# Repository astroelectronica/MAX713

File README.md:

# MAX713
NiCd/NiMH Battery Fast-Charge Controller

AE01012713

https://www.analog.com/en/products/max713.html

https://www.analog.com/en/resources/evaluation-hardware-and-software/evaluation-boards-kits/max713swevkit.html

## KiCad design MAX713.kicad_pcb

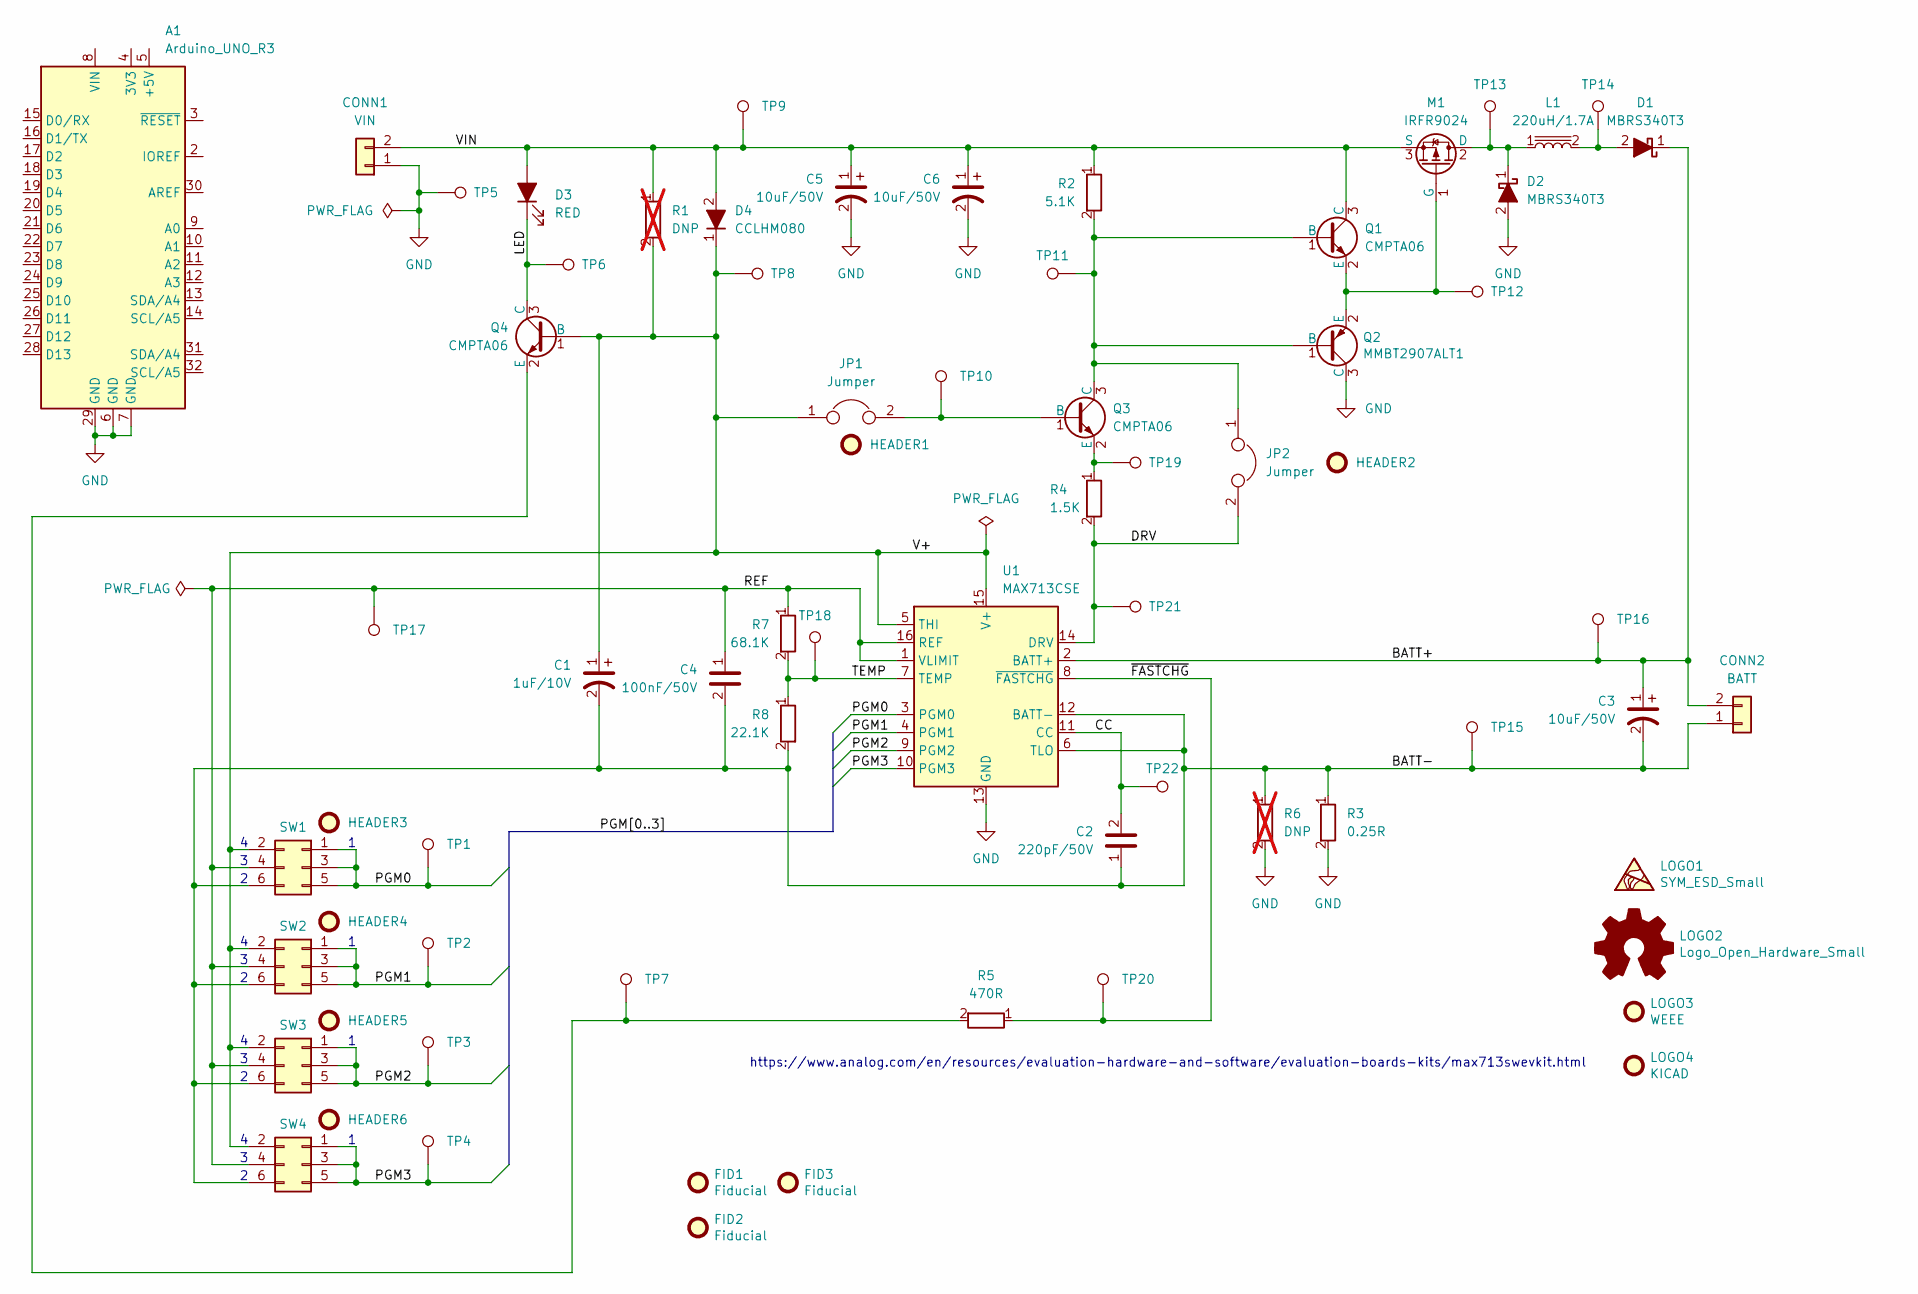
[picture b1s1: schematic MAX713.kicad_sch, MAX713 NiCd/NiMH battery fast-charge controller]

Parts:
A1: Arduino_UNO_R3; Arduino_UNO_R3_WithMountingHoles
C1: 1uF/10V; CP_EIA-3528-21_Kemet-B; MPN 595D105X9035A2T
C2: 220pF/50V; C_0805_2012Metric; MPN C0805C221J5GACTU
C3, C5, C6: 10uF/50V; CP_EIA-7260-38_AVX-R; MPN 595D106X0050R2T
C4: 100nF/50V; C_0805_2012Metric; MPN C0805C101J5GAC7800
CONN1: VIN; TerminalBlock_Phoenix_MKDS-1,5-2-5.08_1x02_P5.08mm_Horizont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; MPN 1985865
CONN2: BATT; TerminalBlock_Phoenix_MKDS-1,5-2-5.08_1x02_P5.08mm_Horizont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; MPN 1985865
D1, D2: MBRS340T3; D_SMC; MPN MBRS340T3G
D3: RED; LED_1206_3216Metric_ReverseMount_Hole1.8x2.4mm; MPN SML-211UTT86
D4: CCLHM080; D_MiniMELF; MPN CMJH080 TR PBFREE
FID1, FID2, FID3: Fiducial; Fiducial_1mm_Mask2mm
HEADER1, HEADER2, HEADER3, HEADER4, HEADER5, HEADER6: 929950-00; MPN 929950-00
JP1, JP2: Jumper; PinHeader_1x02_P2.54mm_Vertical; MPN 5-146281-2
L1: 220uH/1.7A; L_Bourns_SRR1210A; MPN SRR1210-221M
LOGO1: SYM_ESD_Small; ESD-Logo_6.6x6mm_SilkScreen
LOGO2: Logo_Open_Hardware_Small; OSHW-Logo_5.7x6mm_SilkScreen
LOGO3: WEEE; WEEE-Logo_4.2x6mm_SilkScreen
LOGO4: KICAD; KiCad-Logo2_5mm_SilkScreen
M1: IRFR9024; TO-252-2; MPN IRFR9024TRPBF
Q1, Q3, Q4: CMPTA06; SOT-23; MPN CMPTA06 TR PBFREE
Q2: MMBT2907ALT1; SOT-23; MPN MMBT2907ALT1G
R1, R6: DNP; R_Axial_DIN0922_L20.0mm_D9.0mm_P30.48mm_Horizontal; not fitted
R2: 5.1K; R_0805_2012Metric; MPN CRCW08055K10FKEA
R3: 0.25R; R_2512_6332Metric; MPN WSL2512R2500FEA
R4: 1.5K; R_0805_2012Metric; MPN CRCW08051K50FKEA
R5: 470R; R_0805_2012Metric; MPN CRCW0805470RFKEA
R7: 68.1K; R_0805_2012Metric; MPN CRCW080568K1FKEA
R8: 22.1K; R_0805_2012Metric; MPN CRCW080522K1FKEA
SW1: SW1; PinHeader_2x03_P2.54mm_Vertical; MPN 67996-206HLF
SW2: SW2; PinHeader_2x03_P2.54mm_Vertical; MPN 67996-206HLF
SW3: SW3; PinHeader_2x03_P2.54mm_Vertical; MPN 67996-206HLF
SW4: SW4; PinHeader_2x03_P2.54mm_Vertical; MPN 67996-206HLF
TP1, TP2, TP3, TP4, TP5, TP6, TP7, TP8, TP9, TP10, TP11, TP12, TP13, TP14, TP15, TP16, TP17, TP18, TP19, TP20, TP21, TP22: TestPoint; TestPoint_Pad_D1.5mm
U1: MAX713CSE; SOIC-16_3.9x9.9mm_P1.27mm; MPN MAX713CSE+

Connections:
/BATT+: C3.1, CONN2.2, D1.1 (K), TP16.1, U1.2 (BATT+)
/BATT-: C1.2, C2.1, C3.2, C4.2, CONN2.1, R3.1, R6.1, R8.2, SW1.6, SW2.6, SW3.6, SW4.6, TP15.1, U1.6 (TLO), U1.12 (BATT-)
/CC: C2.2, TP22.1, U1.11 (CC)
/DRV: JP2.2, R4.2, TP21.1, U1.14 (DRV)
/LED: D3.1 (K), Q4.3 (C), TP6.1
/PGM0: SW1.1, SW1.3, SW1.5, TP1.1, U1.3 (PGM0)
/PGM1: SW2.1, SW2.3, SW2.5, TP2.1, U1.4 (PGM1)
/PGM2: SW3.1, SW3.3, SW3.5, TP3.1, U1.9 (PGM2)
/PGM3: SW4.1, SW4.3, SW4.5, TP4.1, U1.10 (PGM3)
/REF: C4.1, R7.1, SW1.4, SW2.4, SW3.4, SW4.4, TP17.1, U1.1 (VLIMIT), U1.16 (REF)
/TEMP: R7.2, R8.1, TP18.1, U1.7 (TEMP)
/V+: C1.1, D4.1 (K), JP1.1, Q4.1 (B), R1.2, SW1.2, SW2.2, SW3.2, SW4.2, TP8.1, U1.5 (THI), U1.15 (V+)
/VIN: C5.1, C6.1, CONN1.2, D3.2 (A), D4.2 (A), M1.3 (S), Q1.3 (C), R1.1, R2.1, TP9.1
/~FASTCHG: R5.1, TP20.1, U1.8 (~FASTCHG)
GND: A1.6 (GND), A1.7 (GND), A1.29 (GND), C5.2, C6.2, CONN1.1, D2.2 (A), Q2.3 (C), R3.2, R6.2, TP5.1, U1.13 (GND)
unnamed: D1.2 (A), L1.2, TP14.1
unnamed: D2.1 (K), L1.1, M1.2 (D), TP13.1
unnamed: M1.1 (G), Q1.2 (E), Q2.2 (E), TP12.1
unnamed: JP2.1, Q1.1 (B), Q2.1 (B), Q3.3 (C), R2.2, TP11.1
unnamed: JP1.2, Q3.1 (B), TP10.1
unnamed: Q3.2 (E), R4.1, TP19.1
unnamed: Q4.2 (E), R5.2, TP7.1

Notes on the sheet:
https://www.analog.com/en/resources/evaluation-hardware-and-software/evaluation-boards-kits/max713swevkit.html

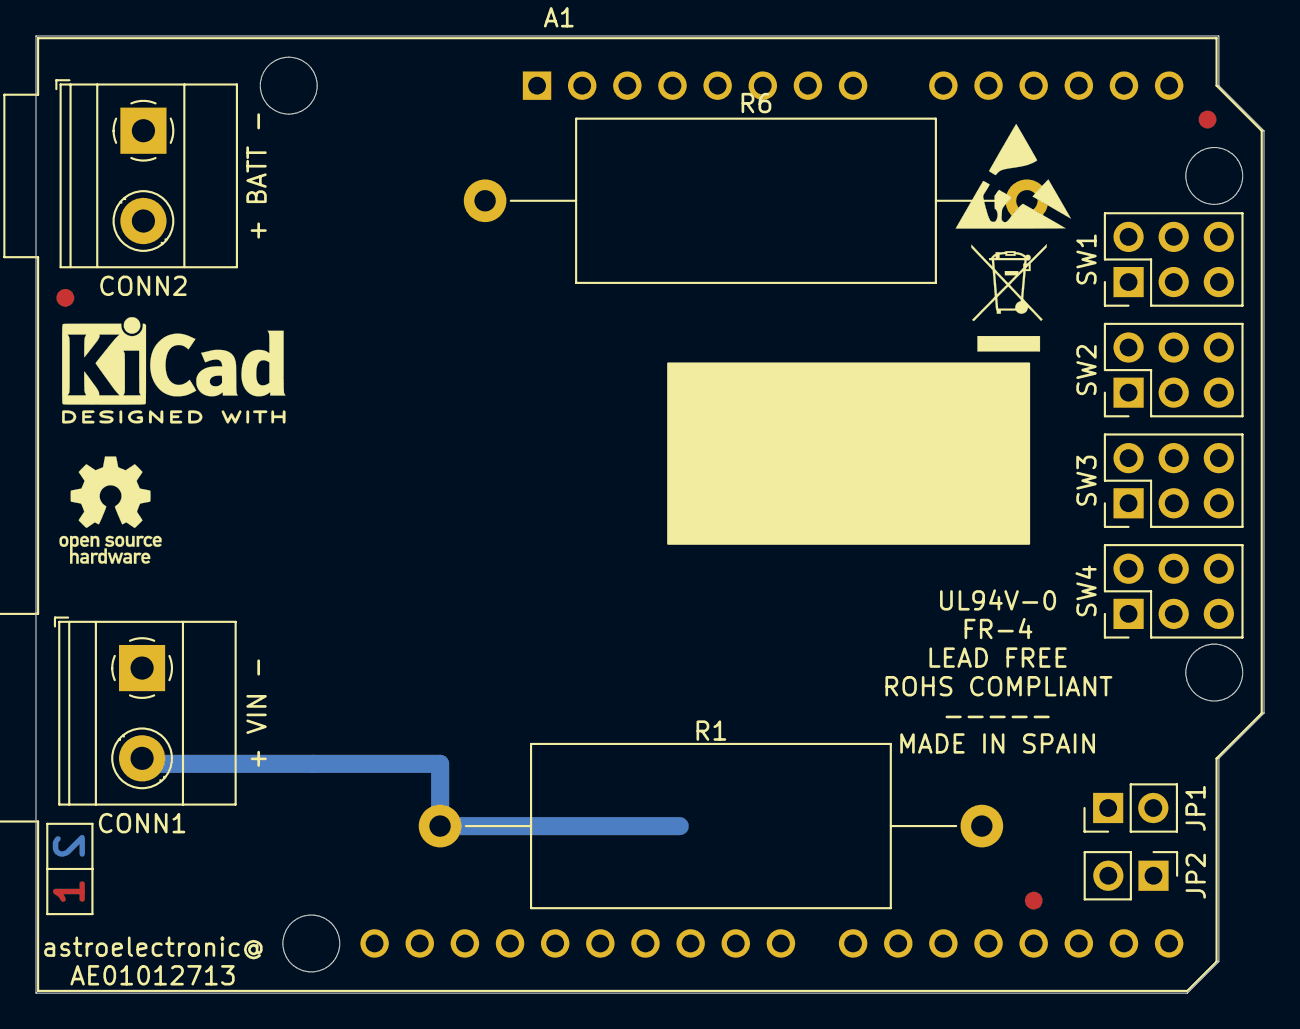
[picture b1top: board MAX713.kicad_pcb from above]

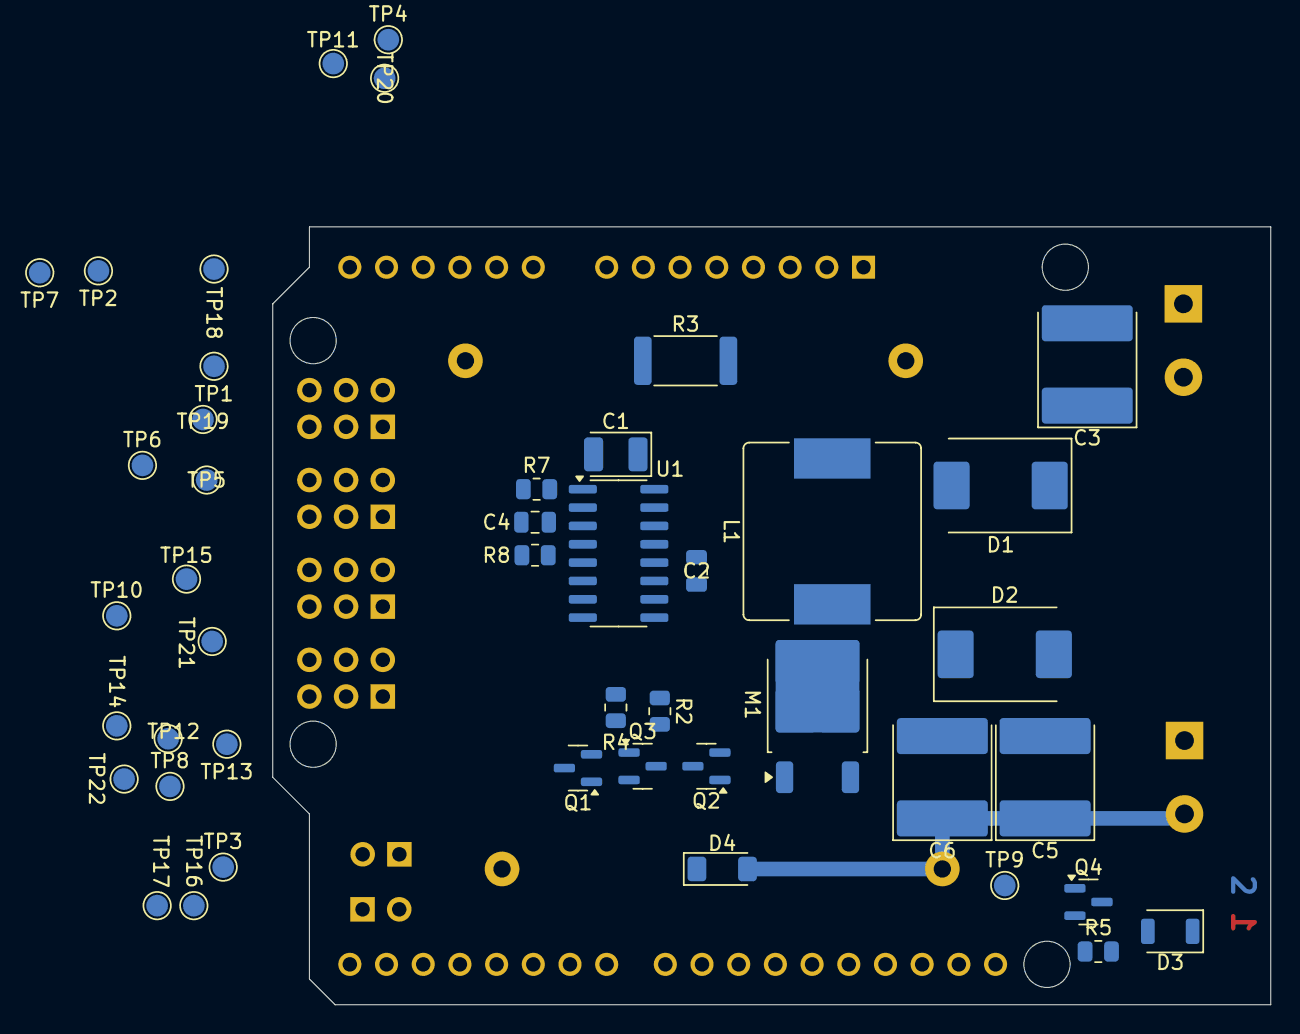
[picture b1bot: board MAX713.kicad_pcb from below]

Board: 2 copper layers, 69.1 x 53.8 mm, 63 parts (45 on the bottom side), 22 nets.

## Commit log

2024-12-13 Add files via upload
    BOM octopart and digikey
2024-12-13 Update README.md
    manufacturer page link
